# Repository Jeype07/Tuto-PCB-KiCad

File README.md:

# Tuto-PCB-KiCad

These are the results of a small tutorial on how to make a PCB using the sofware Kicad 8 (Schematics and Routing).
We are going to build a PCB around the microcontroller  STM32G431KBT6 (not available in Kicad libraries), supplied by a USB port to enable the communication with a PC.

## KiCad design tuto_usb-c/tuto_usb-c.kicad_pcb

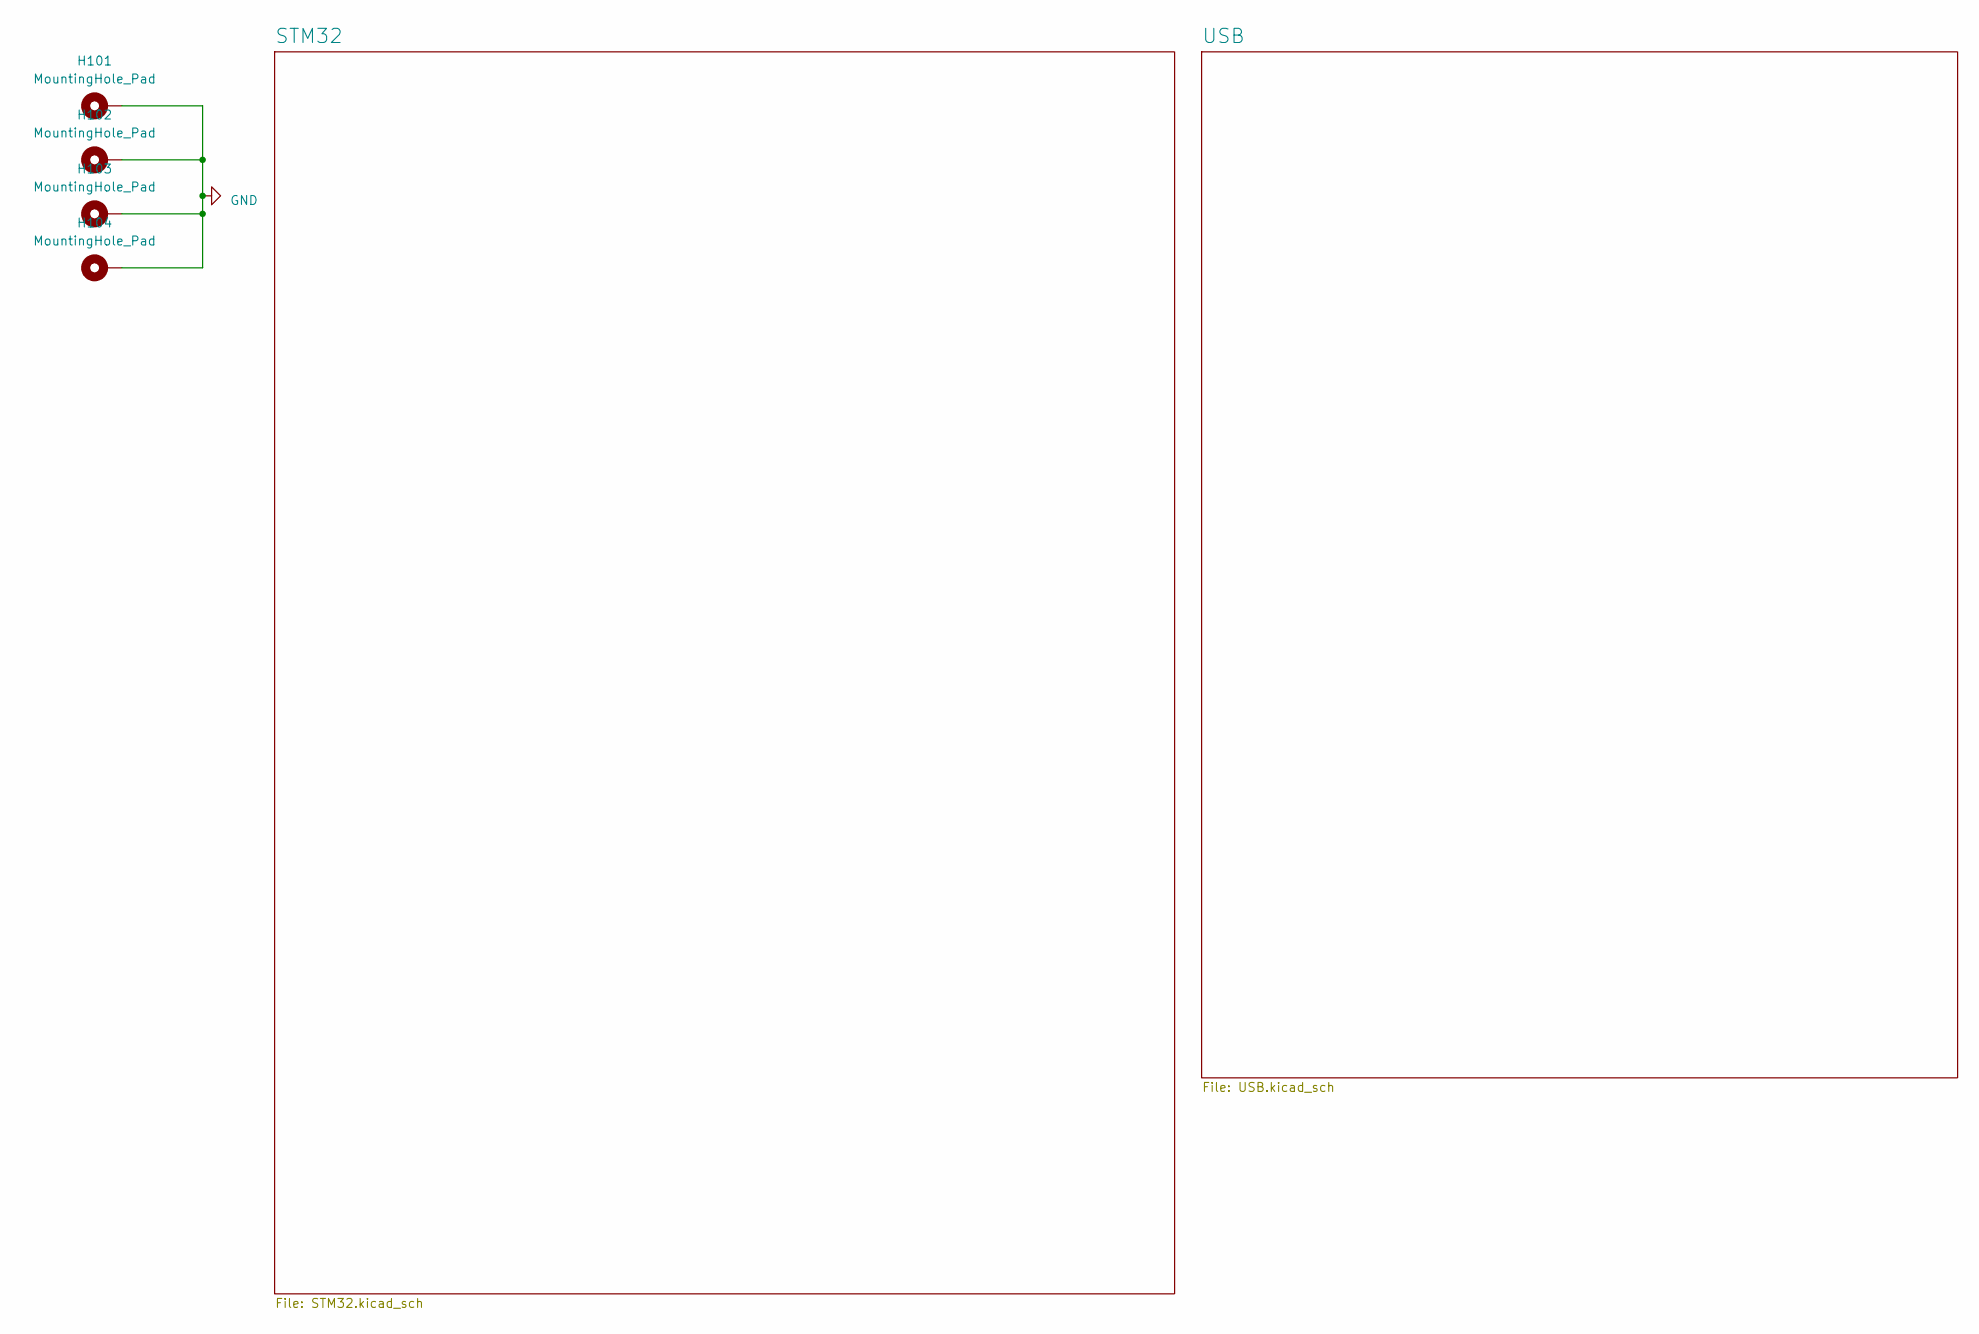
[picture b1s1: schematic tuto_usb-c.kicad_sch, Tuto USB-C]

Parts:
H101, H102, H103, H104: MountingHole_Pad; MountingHole_3.2mm_M3_Pad_Via

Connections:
GND: H101.1, H102.1, H103.1, H104.1; also elsewhere on the board

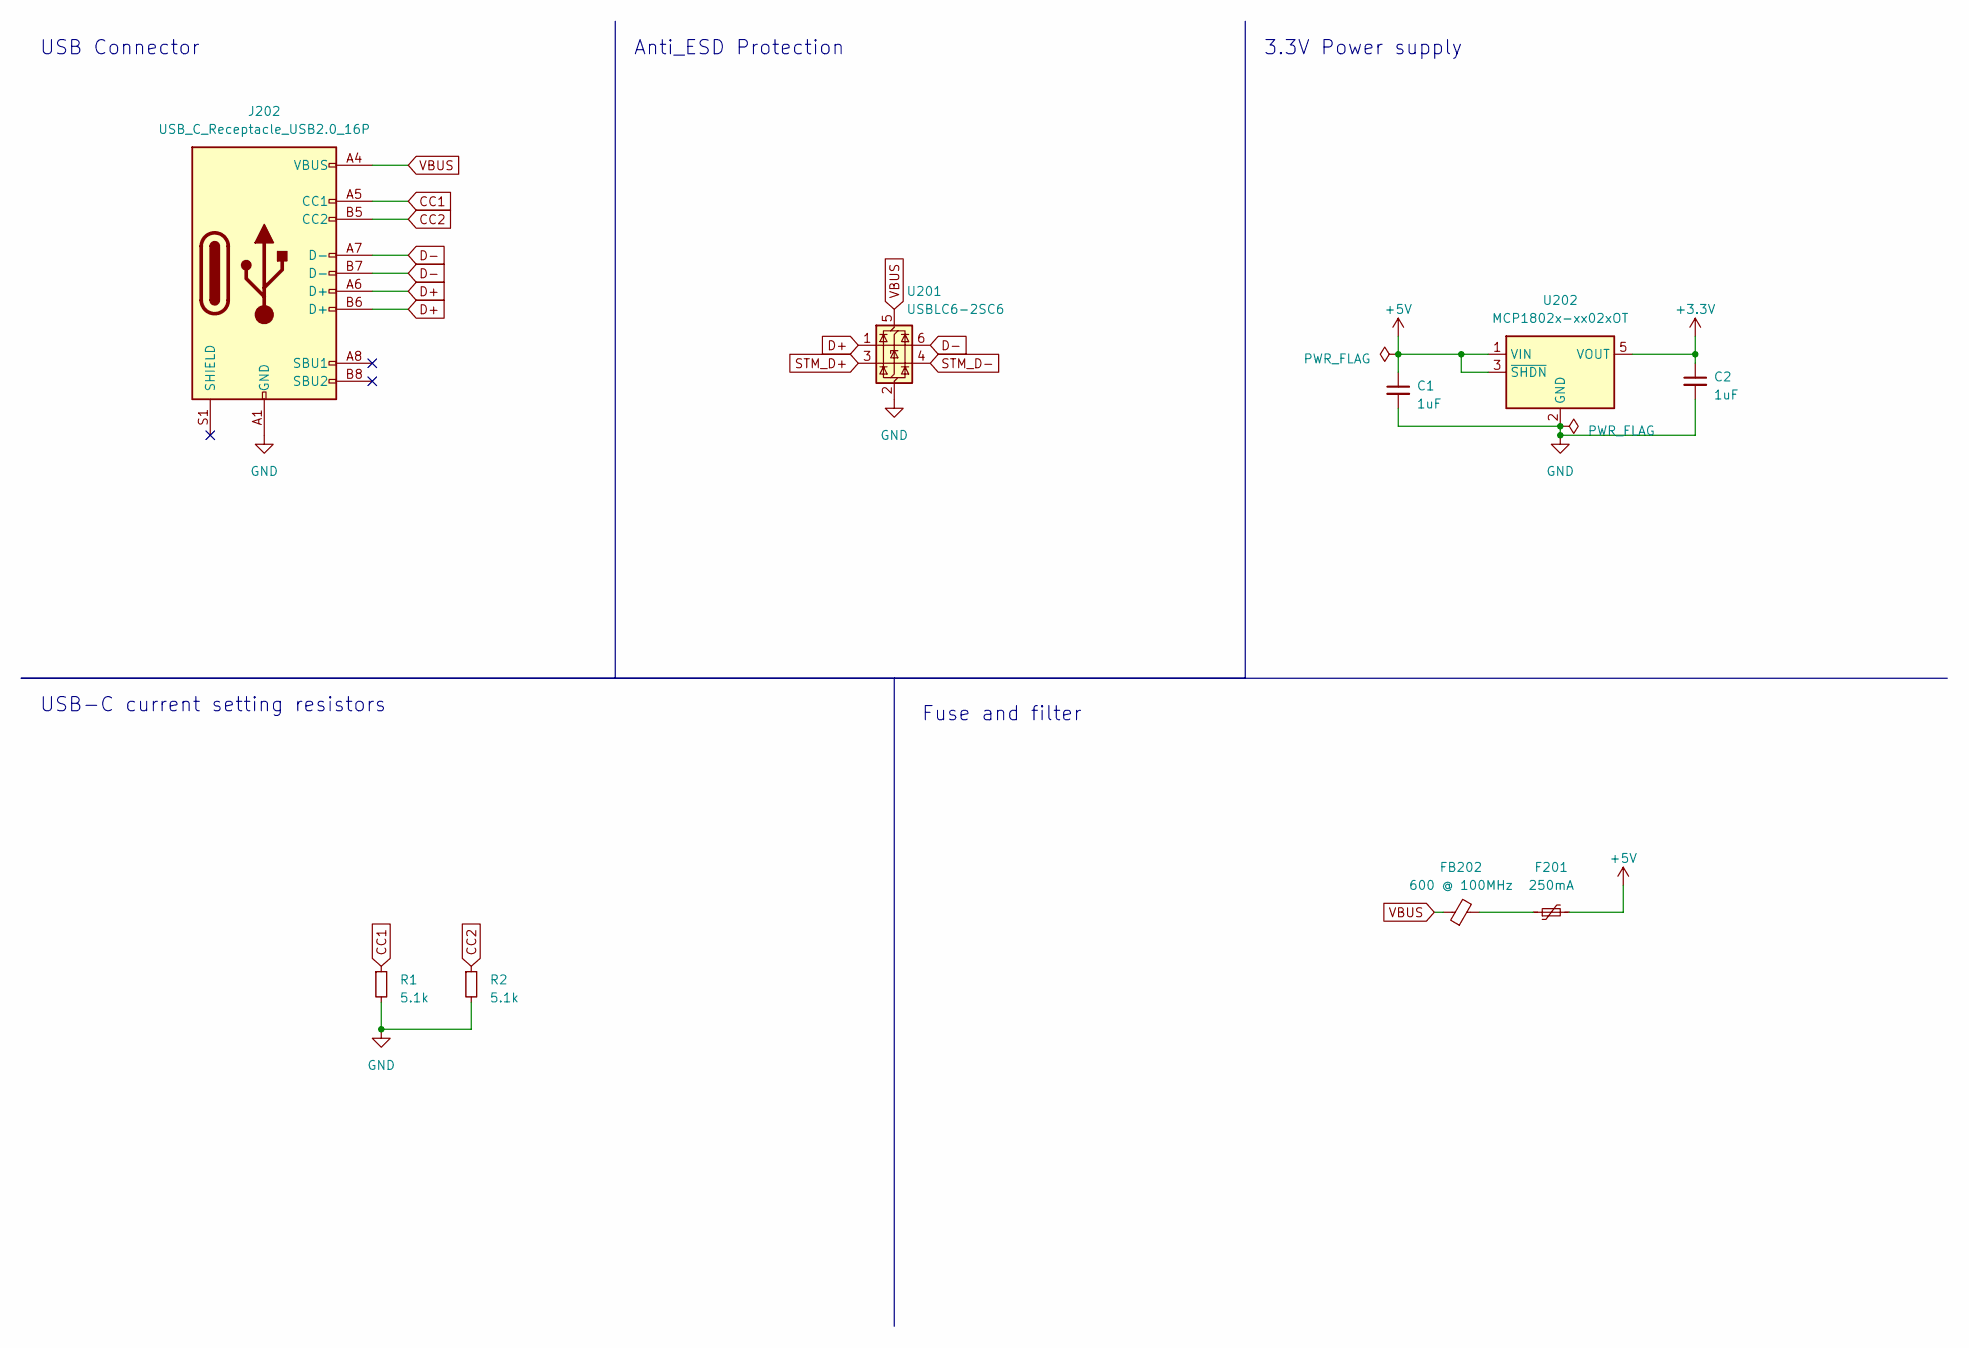
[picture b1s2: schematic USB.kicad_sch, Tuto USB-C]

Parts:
C1, C2: 1uF; C_0603_1608Metric_Pad1.08x0.95mm_HandSolder
F201: 250mA; Fuse_1206_3216Metric
FB202: 600 @ 100MHz; L_0805_2012Metric
J202: USB_C_Receptacle_USB2.0_16P; USB_C_Receptacle_HRO_TYPE-C-31-M-12
R1, R2: 5.1k; R_0603_1608Metric_Pad0.98x0.95mm_HandSolder
U201: USBLC6-2SC6; SOT-23-6
U202: MCP1802x-xx02xOT; SOT-23-5

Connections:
+3.3V: C2.1, U202.5 (VOUT); also elsewhere on the board
+5V: C1.1, F201.2, U202.1 (VIN), U202.3 (~SHDN)
CC1: J202.A5 (CC1), R1.1
CC2: J202.B5 (CC2), R2.1
D+: J202.A6 (D+), J202.B6 (D+), U201.1 (I/O1)
D-: J202.A7 (D-), J202.B7 (D-), U201.6 (I/O1)
GND: C1.2, C2.2, J202.A1 (GND), J202.A12 (GND), J202.B1 (GND), J202.B12 (GND), R1.2, R2.2, U201.2 (GND), U202.2 (GND); also elsewhere on the board
unnamed: F201.1, FB202.2
STM_D+: U201.3 (I/O2); also elsewhere on the board
STM_D-: U201.4 (I/O2); also elsewhere on the board
VBUS: FB202.1, J202.A4 (VBUS), J202.A9 (VBUS), J202.B4 (VBUS), J202.B9 (VBUS), U201.5 (VBUS)

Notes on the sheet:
Anti_ESD Protection
USB Connector
USB-C current setting resistors
3.3V Power supply
Fuse and filter

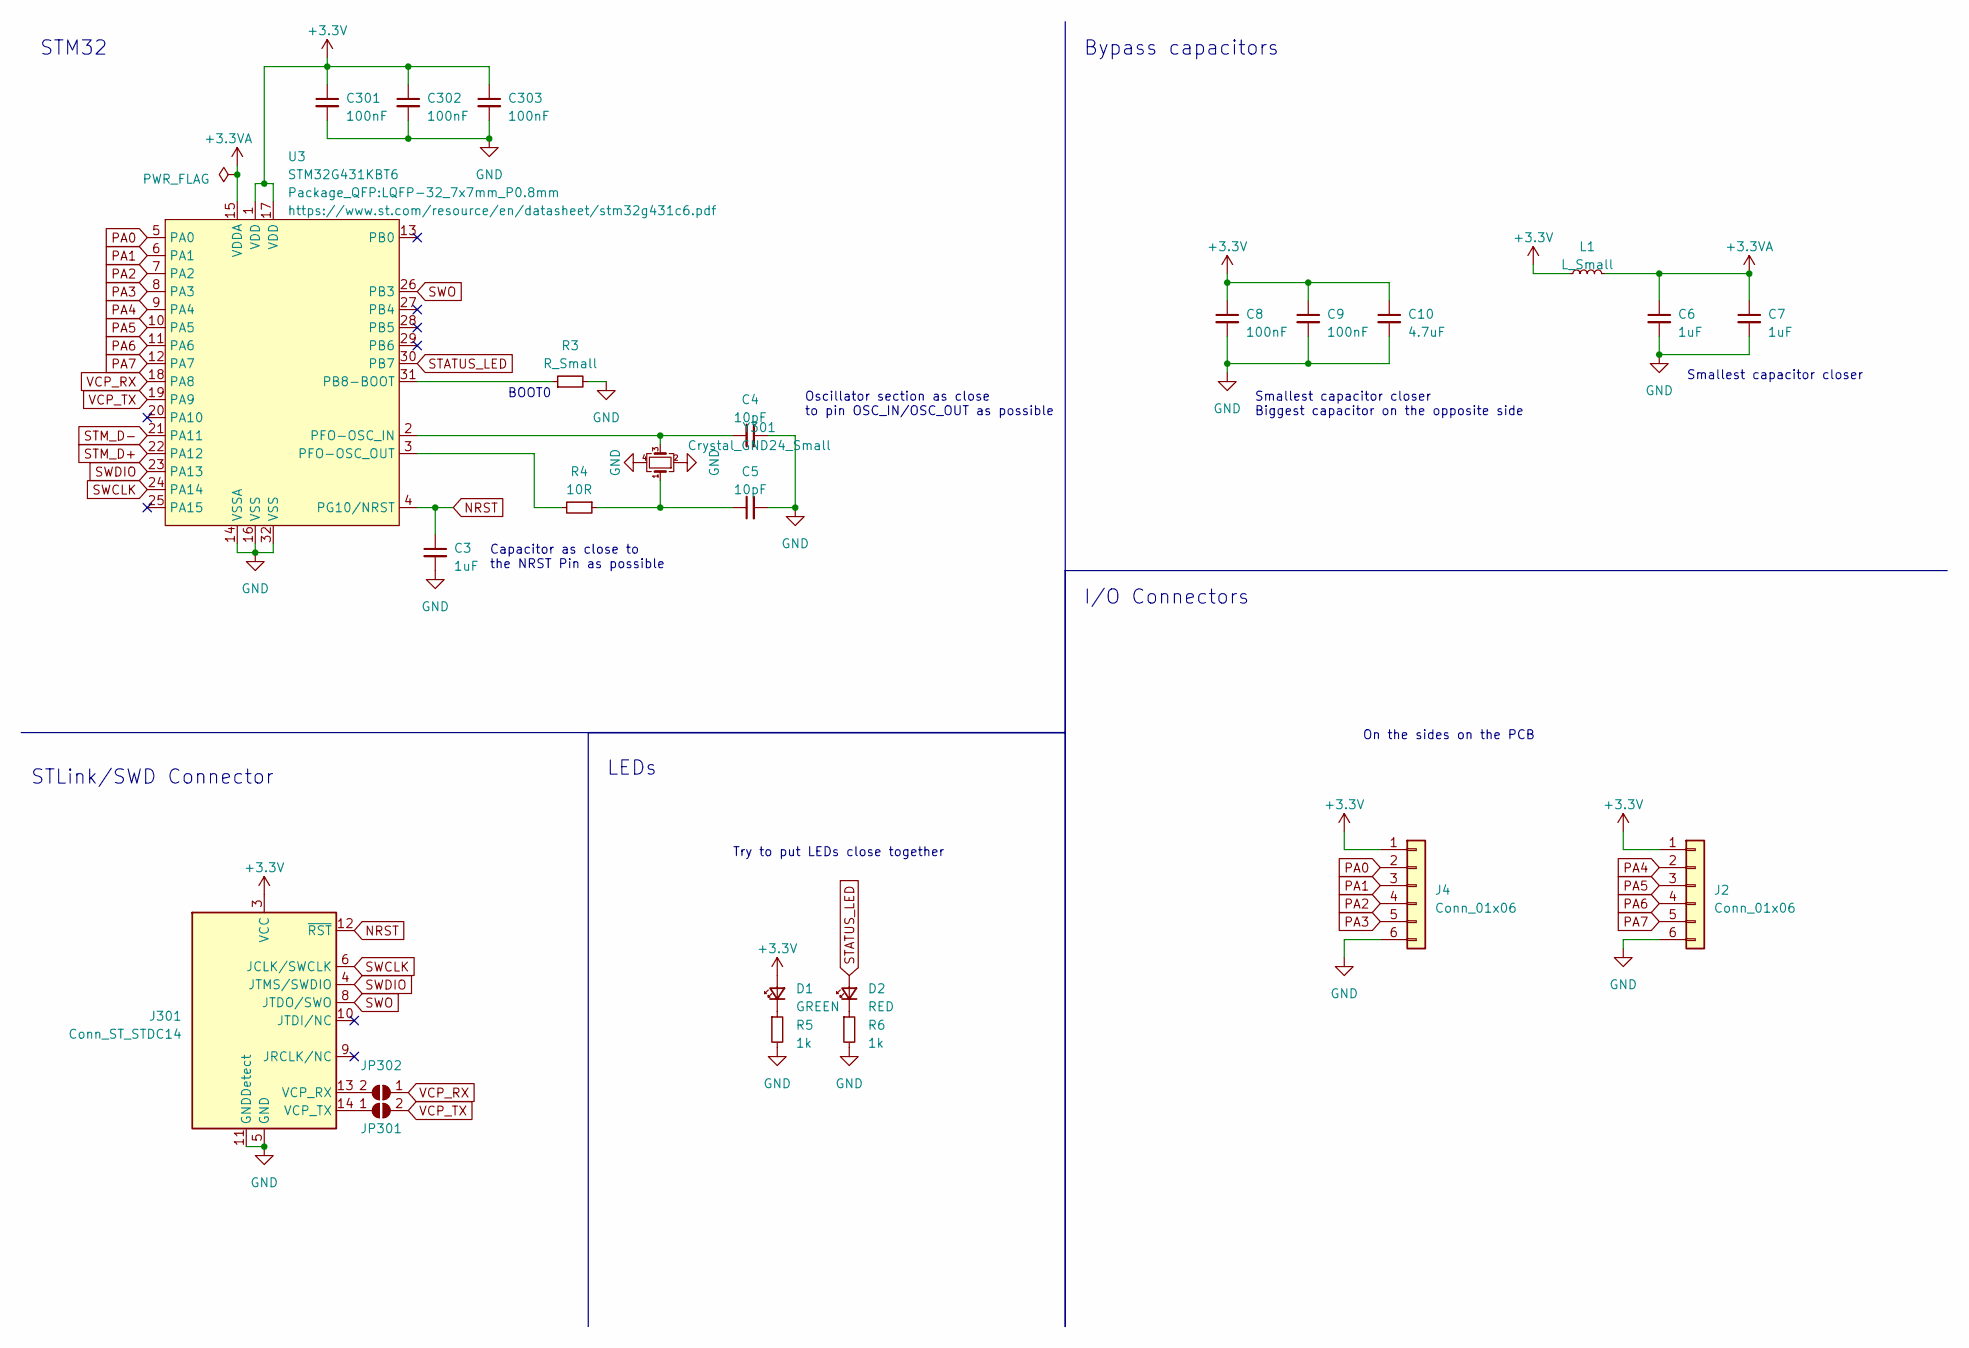
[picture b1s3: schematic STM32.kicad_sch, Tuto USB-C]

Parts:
C3, C6, C7: 1uF; C_0603_1608Metric_Pad1.08x0.95mm_HandSolder
C4, C5: 10pF; C_0603_1608Metric_Pad1.08x0.95mm_HandSolder
C8, C9, C301, C302, C303: 100nF; C_0603_1608Metric_Pad1.08x0.95mm_HandSolder
C10: 4.7uF; C_0603_1608Metric_Pad1.08x0.95mm_HandSolder
D1: GREEN; LED_0603_1608Metric_Pad1.05x0.95mm_HandSolder
D2: RED; LED_0603_1608Metric_Pad1.05x0.95mm_HandSolder
J2, J4: Conn_01x06; PinHeader_1x06_P2.54mm_Vertical
J301: Conn_ST_STDC14; PinHeader_2x07_P1.27mm_Vertical_SMD
JP301, JP302: SolderJumper_2_Open; SolderJumper-2_P1.3mm_Open_TrianglePad1.0x1.5mm
L1: L_Small; R_0603_1608Metric_Pad0.98x0.95mm_HandSolder
R3: R_Small; R_0603_1608Metric_Pad0.98x0.95mm_HandSolder
R4: 10R; R_0603_1608Metric_Pad0.98x0.95mm_HandSolder
R5, R6: 1k; R_0603_1608Metric_Pad0.98x0.95mm_HandSolder
U3: STM32G431KBT6; LQFP-32_7x7mm_P0.8mm
Y301: Crystal_GND24_Small; Crystal_SMD_0603-4Pin_6.0x3.5mm

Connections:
+3.3V: C8.1, C9.1, C10.1, C301.1, C302.1, C303.1, D1.2 (A), J2.1, J4.1, J301.3 (VCC), L1.1, U3.1 (VDD), U3.17 (VDD); also elsewhere on the board
+3.3VA: C6.1, C7.1, L1.2, U3.15 (VDDA)
GND: C3.2, C4.1, C5.2, C6.2, C7.2, C8.2, C9.2, C10.2, C301.2, C302.2, C303.2, J2.6, J4.6, J301.5 (GND), J301.7 (GND), J301.11 (GNDDetect), R3.2, R5.2, R6.2, U3.14 (VSSA), U3.16 (VSS), U3.32 (VSS), Y301.2, Y301.4; also elsewhere on the board
NRST: C3.1, J301.12 (~RST), U3.4 (PG10/NRST)
unnamed: C5.1, R4.1, Y301.1
unnamed: D1.1 (K), R5.1
unnamed: D2.1 (K), R6.1
unnamed: J301.13 (VCP_RX), JP302.2 (B)
unnamed: J301.14 (VCP_TX), JP301.1 (A)
unnamed: R3.1, U3.31 (PB8-BOOT)
unnamed: C4.2, U3.2 (PFO-OSC_IN), Y301.3
unnamed: R4.2, U3.3 (PFO-OSC_OUT)
PA0: J4.2, U3.5 (PA0)
PA1: J4.3, U3.6 (PA1)
PA2: J4.4, U3.7 (PA2)
PA3: J4.5, U3.8 (PA3)
PA4: J2.2, U3.9 (PA4)
PA5: J2.3, U3.10 (PA5)
PA6: J2.4, U3.11 (PA6)
PA7: J2.5, U3.12 (PA7)
STATUS_LED: D2.2 (A), U3.30 (PB7)
STM_D+: U3.22 (PA12); also elsewhere on the board
STM_D-: U3.21 (PA11); also elsewhere on the board
SWCLK: J301.6 (JCLK/SWCLK), U3.24 (PA14)
SWDIO: J301.4 (JTMS/SWDIO), U3.23 (PA13)
SWO: J301.8 (JTDO/SWO), U3.26 (PB3)
VCP_RX: JP302.1 (A), U3.18 (PA8)
VCP_TX: JP301.2 (B), U3.19 (PA9)

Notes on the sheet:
STM32
Bypass capacitors
Oscillator section as close to pin OSC_IN/OSC_OUT as possible
LEDs
On the sides on the PCB
Try to put LEDs close together
Smallest capacitor closer Biggest capacitor on the opposite side
Smallest capacitor closer
STLink/SWD Connector
Capacitor as close to the NRST Pin as possible
BOOT0
I/O Connectors

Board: 4 copper layers, 38 parts (0 on the bottom side), 35 nets, no tracks yet.

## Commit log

2024-10-08 Add project
2024-10-08 modif routing - add gng plane
2024-10-13 placement des composants sur la PCB
